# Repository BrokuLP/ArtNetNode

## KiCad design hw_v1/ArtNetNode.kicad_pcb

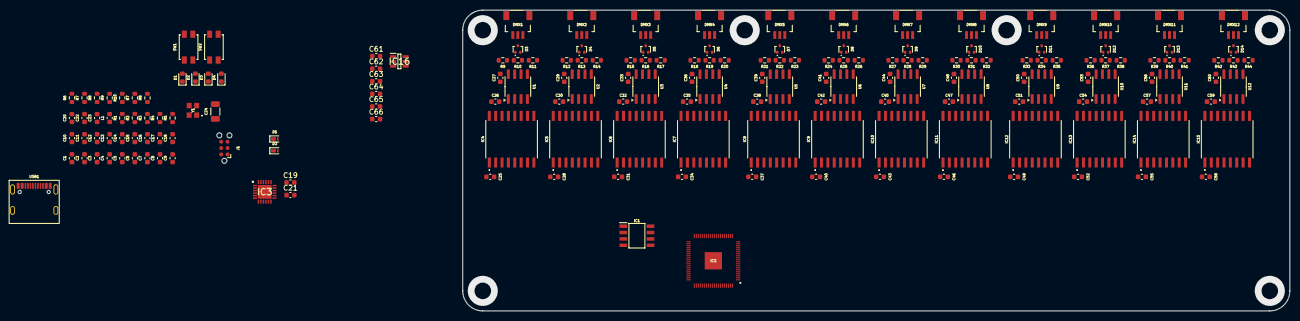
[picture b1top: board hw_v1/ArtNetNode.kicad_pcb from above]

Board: 4 copper layers, 165.0 x 60.0 mm, 178 parts (0 on the bottom side), 149 nets, no tracks yet.

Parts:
C1, C2, C6, C8, C9, C10, C11, C12, C13, C14, C15, C16, C17, C18, C19, C20, C21, C22, C23: 0u1/6V3; C_0603_1608Metric
C3, C4, C5, C7: 4u7/6V3; C_0603_1608Metric
C24: 1n/2kV; C_1206_3216Metric
C25, C26, C28, C29, C31, C32, C34, C35, C37, C38, C40, C41, C43, C44, C46, C47, C49, C50, C52, C53, C55, C56, C58, C59, C61, C62, C63, C64, C65, C66: 10u/6V3; C_0603_1608Metric
C27, C30, C33, C36, C39, C42, C45, C48, C51, C54, C57, C60: 1u/6V3; C_0603_1608Metric
D1, D2#2, D3#2, D4: LED; LED_0603_1608Metric
D1#2, D2: PTVS5V0Z1USK; Nexperia_DSN1608-2_1.6x0.8mm
D3, D4#2, D5, D6, D7, D8, D9, D10, D11, D12, D13, D14: RCLAMP0502B; SOT-416
DMX1, DMX2, DMX3, DMX4, DMX5, DMX6, DMX7, DMX8, DMX9, DMX10, DMX11, DMX12: SM03B-SRSS-TB_LF__SN_; SM03BSRSSTBLFSN
IC1: W25Q16JVSNIQ; SOIC127P600X175-8N
IC2: RP2350B; QFN40P1000X1000X90-81N-D
IC3: KTS1622EUAA-TR; QFN50P400X400X80-25N-D
IC4, IC5, IC6, IC7, IC8, IC9, IC10, IC11, IC12, IC13, IC14, IC15: 18024215401H
IC16: TPP361063-T6TR; SOT95P280X95-6N
J1: Conn_ARM_SWD_TagConnect_TC2030-NL; Tag-Connect_TC2030-IDC-NL_2x03_P1.27mm_Vertical
L1: 3u3; C_0603_1608Metric
R1, R7#2, R8, R9#2, R10: 10k; R_0603_1608Metric
R2, R6: 1k; R_0603_1608Metric
R3, R4: 27; R_0603_1608Metric
R5: 33; R_0603_1608Metric
R7, R8#2: 5k1; R_0603_1608Metric
R9, R10#2, R11, R12, R13, R14, R15, R16, R17, R18, R19, R20, R21, R22, R23, R24, R25, R26, R27, R28, R29, R30, R31, R32, R33, R34, R35, R36, R37, R38, R39, R40, R41, R42, R43, R44: R; R_0603_1608Metric
SW1, SW2: SW_SPST; SW_SPST_EVQP2
U1, U2, U3, U4, U5, U6, U7, U8, U9, U10, U11, U12: ST485E; SOIC-8_3.9x4.9mm_P1.27mm
USB1: USB4105-GF-A
Y1: SiT1602AC-13-33E-12.000000; SiT1602_2.5x2mm

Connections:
1V1: C4.1, C5.1, C6.1, C8.1, C9.1, IC2.10 (DVDD_1), IC2.32 (DVDD_2), IC2.51 (DVDD_3), IC2.65 (VREG_FB), L1.1
3V3: C1.1, C2.1, C3.1, C10.1, C11.1, C13.1, C14.1, C15.1, C16.1, C17.1, C18.1, C19.1, C20.1, C21.1, C22.1, C23.1, IC1.8 (VCC), IC2.5 (IOVDD_1), IC2.15 (IOVDD_2), IC2.24 (IOVDD_3), IC2.29 (IOVDD_4), IC2.41 (IOVDD_5), IC2.50 (IOVDD_6), IC2.59 (ADC_AVDD), IC2.60 (IOVDD_7), IC2.64 (VREG_VIN), IC2.68 (USB_OTP_VDD), IC2.69 (QSPI_IOVDD), IC2.76 (IOVDD_8), IC3.21 (VDD_P), IC3.23 (VDD_I2C), R1.1, R5.1, R6.1, Y1.1 (OE/~ST/NC), Y1.4 (VDD)
5V: J1.1 (VCC), USB1.A4 (VBUS), USB1.A9 (VBUS)
5V0: C25.1, C28.1, C31.1, C34.1, C37.1, C40.1, C43.1, C46.1, C49.1, C52.1, C55.1, C58.1, IC4.1 (VCC), IC5.1 (VCC), IC6.1 (VCC), IC7.1 (VCC), IC8.1 (VCC), IC9.1 (VCC), IC10.1 (VCC), IC11.1 (VCC), IC12.1 (VCC), IC13.1 (VCC), IC14.1 (VCC), IC15.1 (VCC)
/DMX0_RXD: IC2.13 (GPIO14), IC4.5 (OUTC)
/DMX0_TXD: IC2.11 (GPIO12), IC4.4 (INB)
/DMX0_TXE: IC2.12 (GPIO13), IC4.3 (INA)
/DMX1_RXD: IC2.17 (GPIO17), IC5.5 (OUTC)
/DMX1_TXD: IC2.16 (GPIO16), IC5.4 (INB)
/DMX1_TXE: IC2.14 (GPIO15), IC5.3 (INA)
/DMX2_RXD: IC2.20 (GPIO20), IC6.5 (OUTC)
/DMX2_TXD: IC2.18 (GPIO18), IC6.4 (INB)
/DMX2_TXE: IC2.19 (GPIO19), IC6.3 (INA)
/DMX3_RXD: IC2.23 (GPIO23), IC7.5 (OUTC)
/DMX3_TXD: IC2.21 (GPIO21), IC7.4 (INB)
/DMX3_TXE: IC2.22 (GPIO22), IC7.3 (INA)
/DMX4_RXD: IC2.27 (GPIO26), IC8.5 (OUTC)
/DMX4_TXD: IC2.25 (GPIO24), IC8.4 (INB)
/DMX4_TXE: IC2.26 (GPIO25), IC8.3 (INA)
/DMX5_RXD: IC2.37 (GPIO29), IC9.5 (OUTC)
/DMX5_TXD: IC2.28 (GPIO27), IC9.4 (INB)
/DMX5_TXE: IC2.36 (GPIO28), IC9.3 (INA)
/DMX6_RXD: IC2.40 (GPIO32), IC10.5 (OUTC)
/DMX6_TXD: IC2.38 (GPIO30), IC10.4 (INB)
/DMX6_TXE: IC2.39 (GPIO31), IC10.3 (INA)
/DMX7_RXD: IC2.44 (GPIO35), IC11.5 (OUTC)
/DMX7_TXD: IC2.42 (GPIO33), IC11.4 (INB)
/DMX7_TXE: IC2.43 (GPIO34), IC11.3 (INA)
/DMX8_RXD: IC2.47 (GPIO38), IC12.5 (OUTC)
/DMX8_TXD: IC2.45 (GPIO36), IC12.4 (INB)
/DMX8_TXE: IC2.46 (GPIO37), IC12.3 (INA)
/DMX9_RXD: IC2.52 (GPIO41_ADC1), IC13.5 (OUTC)
/DMX9_TXD: IC2.48 (GPIO39), IC13.4 (INB)
/DMX9_TXE: IC2.49 (GPIO40_ADC0), IC13.3 (INA)
/DMX10_RXD: IC2.55 (GPIO44_ADC4), IC14.5 (OUTC)
/DMX10_TXD: IC2.53 (GPIO42_ADC2), IC14.4 (INB)
/DMX10_TXE: IC2.54 (GPIO43_ADC3), IC14.3 (INA)
/DMX11_RXD: IC2.58 (GPIO47_ADC7), IC15.5 (OUTC)
/DMX11_TXD: IC2.56 (GPIO45_ADC5), IC15.4 (INB)
/DMX11_TXE: IC2.57 (GPIO46_ADC6), IC15.3 (INA)
/DMX_CH0/5V_DMX: C26.1, C27.1, IC4.10 (SEL), IC4.16 (VOUT), R9.1, U1.8 (VCC)
/DMX_CH0/DE_5V: IC4.14 (OUTA), U1.3 (DE)
/DMX_CH0/DI_5V: IC4.13 (OUTB), U1.4 (DI)
/DMX_CH0/DMX_N: D3.2 (K2), DMX1.1, R10#2.2, R11.1, U1.6 (A)
/DMX_CH0/DMX_P: D3.1 (K1), DMX1.3, R9.2, R10#2.1, U1.7 (B)
/DMX_CH0/GND_DMX: C26.2, C27.2, D3.3 (A), DMX1.2, DMX1.MP1, DMX1.MP2, IC4.9 (GND2_2), IC4.15 (GND2_1), R11.2, U1.2 (~RE), U1.5 (GND)
/DMX_CH0/RO_5V: IC4.12 (INC), U1.1 (RO)
/DMX_CH1/5V_DMX: C29.1, C30.1, IC5.10 (SEL), IC5.16 (VOUT), R12.1, U2.8 (VCC)
/DMX_CH1/DE_5V: IC5.14 (OUTA), U2.3 (DE)
/DMX_CH1/DI_5V: IC5.13 (OUTB), U2.4 (DI)
/DMX_CH1/DMX_N: D4#2.2 (K2), DMX2.1, R13.2, R14.1, U2.6 (A)
/DMX_CH1/DMX_P: D4#2.1 (K1), DMX2.3, R12.2, R13.1, U2.7 (B)
/DMX_CH1/GND_DMX: C29.2, C30.2, D4#2.3 (A), DMX2.2, DMX2.MP1, DMX2.MP2, IC5.9 (GND2_2), IC5.15 (GND2_1), R14.2, U2.2 (~RE), U2.5 (GND)
/DMX_CH1/RO_5V: IC5.12 (INC), U2.1 (RO)
/DMX_CH2/5V_DMX: C32.1, C33.1, IC6.10 (SEL), IC6.16 (VOUT), R15.1, U3.8 (VCC)
/DMX_CH2/DE_5V: IC6.14 (OUTA), U3.3 (DE)
/DMX_CH2/DI_5V: IC6.13 (OUTB), U3.4 (DI)
/DMX_CH2/DMX_N: D5.2 (K2), DMX3.1, R16.2, R17.1, U3.6 (A)
/DMX_CH2/DMX_P: D5.1 (K1), DMX3.3, R15.2, R16.1, U3.7 (B)
/DMX_CH2/GND_DMX: C32.2, C33.2, D5.3 (A), DMX3.2, DMX3.MP1, DMX3.MP2, IC6.9 (GND2_2), IC6.15 (GND2_1), R17.2, U3.2 (~RE), U3.5 (GND)
/DMX_CH2/RO_5V: IC6.12 (INC), U3.1 (RO)
/DMX_CH3/5V_DMX: C35.1, C36.1, IC7.10 (SEL), IC7.16 (VOUT), R18.1, U4.8 (VCC)
/DMX_CH3/DE_5V: IC7.14 (OUTA), U4.3 (DE)
/DMX_CH3/DI_5V: IC7.13 (OUTB), U4.4 (DI)
/DMX_CH3/DMX_N: D6.2 (K2), DMX4.1, R19.2, R20.1, U4.6 (A)
/DMX_CH3/DMX_P: D6.1 (K1), DMX4.3, R18.2, R19.1, U4.7 (B)
/DMX_CH3/GND_DMX: C35.2, C36.2, D6.3 (A), DMX4.2, DMX4.MP1, DMX4.MP2, IC7.9 (GND2_2), IC7.15 (GND2_1), R20.2, U4.2 (~RE), U4.5 (GND)
/DMX_CH3/RO_5V: IC7.12 (INC), U4.1 (RO)
/DMX_CH4/5V_DMX: C38.1, C39.1, IC8.10 (SEL), IC8.16 (VOUT), R21.1, U5.8 (VCC)
/DMX_CH4/DE_5V: IC8.14 (OUTA), U5.3 (DE)
/DMX_CH4/DI_5V: IC8.13 (OUTB), U5.4 (DI)
/DMX_CH4/DMX_N: D7.2 (K2), DMX5.1, R22.2, R23.1, U5.6 (A)
/DMX_CH4/DMX_P: D7.1 (K1), DMX5.3, R21.2, R22.1, U5.7 (B)
/DMX_CH4/GND_DMX: C38.2, C39.2, D7.3 (A), DMX5.2, DMX5.MP1, DMX5.MP2, IC8.9 (GND2_2), IC8.15 (GND2_1), R23.2, U5.2 (~RE), U5.5 (GND)
/DMX_CH4/RO_5V: IC8.12 (INC), U5.1 (RO)
/DMX_CH5/5V_DMX: C41.1, C42.1, IC9.10 (SEL), IC9.16 (VOUT), R24.1, U6.8 (VCC)
/DMX_CH5/DE_5V: IC9.14 (OUTA), U6.3 (DE)
/DMX_CH5/DI_5V: IC9.13 (OUTB), U6.4 (DI)
/DMX_CH5/DMX_N: D8.2 (K2), DMX6.1, R25.2, R26.1, U6.6 (A)
/DMX_CH5/DMX_P: D8.1 (K1), DMX6.3, R24.2, R25.1, U6.7 (B)
/DMX_CH5/GND_DMX: C41.2, C42.2, D8.3 (A), DMX6.2, DMX6.MP1, DMX6.MP2, IC9.9 (GND2_2), IC9.15 (GND2_1), R26.2, U6.2 (~RE), U6.5 (GND)
/DMX_CH5/RO_5V: IC9.12 (INC), U6.1 (RO)
/DMX_CH6/5V_DMX: C44.1, C45.1, IC10.10 (SEL), IC10.16 (VOUT), R27.1, U7.8 (VCC)
/DMX_CH6/DE_5V: IC10.14 (OUTA), U7.3 (DE)
/DMX_CH6/DI_5V: IC10.13 (OUTB), U7.4 (DI)
/DMX_CH6/DMX_N: D9.2 (K2), DMX7.1, R28.2, R29.1, U7.6 (A)
/DMX_CH6/DMX_P: D9.1 (K1), DMX7.3, R27.2, R28.1, U7.7 (B)
/DMX_CH6/GND_DMX: C44.2, C45.2, D9.3 (A), DMX7.2, DMX7.MP1, DMX7.MP2, IC10.9 (GND2_2), IC10.15 (GND2_1), R29.2, U7.2 (~RE), U7.5 (GND)
/DMX_CH6/RO_5V: IC10.12 (INC), U7.1 (RO)
/DMX_CH7/5V_DMX: C47.1, C48.1, IC11.10 (SEL), IC11.16 (VOUT), R30.1, U8.8 (VCC)
/DMX_CH7/DE_5V: IC11.14 (OUTA), U8.3 (DE)
/DMX_CH7/DI_5V: IC11.13 (OUTB), U8.4 (DI)
/DMX_CH7/DMX_N: D10.2 (K2), DMX8.1, R31.2, R32.1, U8.6 (A)
/DMX_CH7/DMX_P: D10.1 (K1), DMX8.3, R30.2, R31.1, U8.7 (B)
/DMX_CH7/GND_DMX: C47.2, C48.2, D10.3 (A), DMX8.2, DMX8.MP1, DMX8.MP2, IC11.9 (GND2_2), IC11.15 (GND2_1), R32.2, U8.2 (~RE), U8.5 (GND)
/DMX_CH7/RO_5V: IC11.12 (INC), U8.1 (RO)
/DMX_CH8/5V_DMX: C50.1, C51.1, IC12.10 (SEL), IC12.16 (VOUT), R33.1, U9.8 (VCC)
/DMX_CH8/DE_5V: IC12.14 (OUTA), U9.3 (DE)
/DMX_CH8/DI_5V: IC12.13 (OUTB), U9.4 (DI)
/DMX_CH8/DMX_N: D11.2 (K2), DMX9.1, R34.2, R35.1, U9.6 (A)
/DMX_CH8/DMX_P: D11.1 (K1), DMX9.3, R33.2, R34.1, U9.7 (B)
/DMX_CH8/GND_DMX: C50.2, C51.2, D11.3 (A), DMX9.2, DMX9.MP1, DMX9.MP2, IC12.9 (GND2_2), IC12.15 (GND2_1), R35.2, U9.2 (~RE), U9.5 (GND)
/DMX_CH8/RO_5V: IC12.12 (INC), U9.1 (RO)
/DMX_CH9/5V_DMX: C53.1, C54.1, IC13.10 (SEL), IC13.16 (VOUT), R36.1, U10.8 (VCC)
/DMX_CH9/DE_5V: IC13.14 (OUTA), U10.3 (DE)
/DMX_CH9/DI_5V: IC13.13 (OUTB), U10.4 (DI)
/DMX_CH9/DMX_N: D12.2 (K2), DMX10.1, R37.2, R38.1, U10.6 (A)
/DMX_CH9/DMX_P: D12.1 (K1), DMX10.3, R36.2, R37.1, U10.7 (B)
/DMX_CH9/GND_DMX: C53.2, C54.2, D12.3 (A), DMX10.2, DMX10.MP1, DMX10.MP2, IC13.9 (GND2_2), IC13.15 (GND2_1), R38.2, U10.2 (~RE), U10.5 (GND)
/DMX_CH9/RO_5V: IC13.12 (INC), U10.1 (RO)
/DMX_CH10/5V_DMX: C56.1, C57.1, IC14.10 (SEL), IC14.16 (VOUT), R39.1, U11.8 (VCC)
/DMX_CH10/DE_5V: IC14.14 (OUTA), U11.3 (DE)
/DMX_CH10/DI_5V: IC14.13 (OUTB), U11.4 (DI)
/DMX_CH10/DMX_N: D13.2 (K2), DMX11.1, R40.2, R41.1, U11.6 (A)
/DMX_CH10/DMX_P: D13.1 (K1), DMX11.3, R39.2, R40.1, U11.7 (B)
/DMX_CH10/GND_DMX: C56.2, C57.2, D13.3 (A), DMX11.2, DMX11.MP1, DMX11.MP2, IC14.9 (GND2_2), IC14.15 (GND2_1), R41.2, U11.2 (~RE), U11.5 (GND)
/DMX_CH10/RO_5V: IC14.12 (INC), U11.1 (RO)
/DMX_CH11/5V_DMX: C59.1, C60.1, IC15.10 (SEL), IC15.16 (VOUT), R42.1, U12.8 (VCC)
/DMX_CH11/DE_5V: IC15.14 (OUTA), U12.3 (DE)
/DMX_CH11/DI_5V: IC15.13 (OUTB), U12.4 (DI)
/DMX_CH11/DMX_N: D14.2 (K2), DMX12.1, R43.2, R44.1, U12.6 (A)
/DMX_CH11/DMX_P: D14.1 (K1), DMX12.3, R42.2, R43.1, U12.7 (B)
/DMX_CH11/GND_DMX: C59.2, C60.2, D14.3 (A), DMX12.2, DMX12.MP1, DMX12.MP2, IC15.9 (GND2_2), IC15.15 (GND2_1), R44.2, U12.2 (~RE), U12.5 (GND)
/DMX_CH11/RO_5V: IC15.12 (INC), U12.1 (RO)
/MCU/DEV_RST: IC2.8 (GPIO10), IC3.24 (~RESET)
/MCU/EXP_INT: IC2.7 (GPIO9), IC3.22 (~INT)
/MCU/I2C_SCL: IC2.4 (GPIO7), IC3.19 (SCL)
/MCU/I2C_SDA: IC2.6 (GPIO8), IC3.20 (SDA)
/MCU/QSPI_SCLK: IC1.6 (CLK), IC2.71 (QSPI_SCLK)
/MCU/QSPI_SD0: IC1.5 (DI_(IO0)), IC2.72 (QSPI_SD0)
/MCU/QSPI_SD1: IC1.2 (DO_(IO1)), IC2.74 (QSPI_SD1)
/MCU/QSPI_SD2: IC1.3 (~WP_(IO2)), IC2.73 (QSPI_SD2)
/MCU/QSPI_SD3: IC1.7 (~HOLD_OR_/RESET_(IO3)), IC2.70 (QSPI_SD3)
/MCU/QSPI_SS: IC1.1 (~CS), IC2.75 (QSPI_SS), R1.2, R2.1
/MCU/RUN: C12.1, IC2.35 (RUN), J1.3 (~RESET), R6.2, SW2.2 (B)
/MCU/SWCLK: IC2.33 (SWCLK), J1.4 (SWCLK)
/MCU/SWD: IC2.34 (SWDIO), J1.2 (SWDIO)
/MCU/USB_DN: D2.1 (K), R4.1, USB1.A7 (DN1), USB1.B7 (DN2)
/MCU/USB_DP: D1#2.1 (K), R3.1, USB1.A6 (DP1), USB1.B6 (DP2)
/MCU/~USB_BOOT: R2.2, SW1.2 (B)
GND: C1.2, C2.2, C3.2, C4.2, C6.2, C7.2, C8.2, C9.2, C10.2, C11.2, C12.2, C13.2, C14.2, C15.2, C16.2, C17.2, C18.2, C19.2, C20.2, C21.2, C22.2, C23.2, C24.1, C25.2, C28.2, C31.2, C34.2, C37.2, C40.2, C43.2, C46.2, C49.2, C52.2, C55.2, C58.2, D1#2.2 (A), D2.2 (A), IC1.4 (GND), IC2.62 (VREG_PGND), IC2.81 (GND), IC3.9 (GND), IC4.2 (GND1_1), IC4.8 (GND1_2), IC5.2 (GND1_1), IC5.8 (GND1_2), IC6.2 (GND1_1), IC6.8 (GND1_2), IC7.2 (GND1_1), IC7.8 (GND1_2), IC8.2 (GND1_1), IC8.8 (GND1_2), IC9.2 (GND1_1), IC9.8 (GND1_2), IC10.2 (GND1_1), IC10.8 (GND1_2), IC11.2 (GND1_1), IC11.8 (GND1_2), IC12.2 (GND1_1), IC12.8 (GND1_2), IC13.2 (GND1_1), IC13.8 (GND1_2), IC14.2 (GND1_1), IC14.8 (GND1_2), IC15.2 (GND1_1), IC15.8 (GND1_2), IC16.2 (GND), J1.5 (GND), R7.1, R8#2.1, SW1.1 (A), SW2.1 (A), USB1.A1 (GND), USB1.A12 (GND), Y1.2 (GND)
unnamed: IC2.66 (USB_DM), R3.2
unnamed: IC2.67 (USB_DP), R4.2
unnamed: C7.1, IC2.61 (VREG_AVDD), R5.2
unnamed: C5.2, IC2.63 (VREG_LX), L1.2
unnamed: IC2.30 (XIN), Y1.3 (OUT)
unnamed: R7.2, USB1.A5 (CC1)
unnamed: R8#2.2, USB1.B5 (CC2)
unnamed: C24.2, USB1.SH (SHIELD)

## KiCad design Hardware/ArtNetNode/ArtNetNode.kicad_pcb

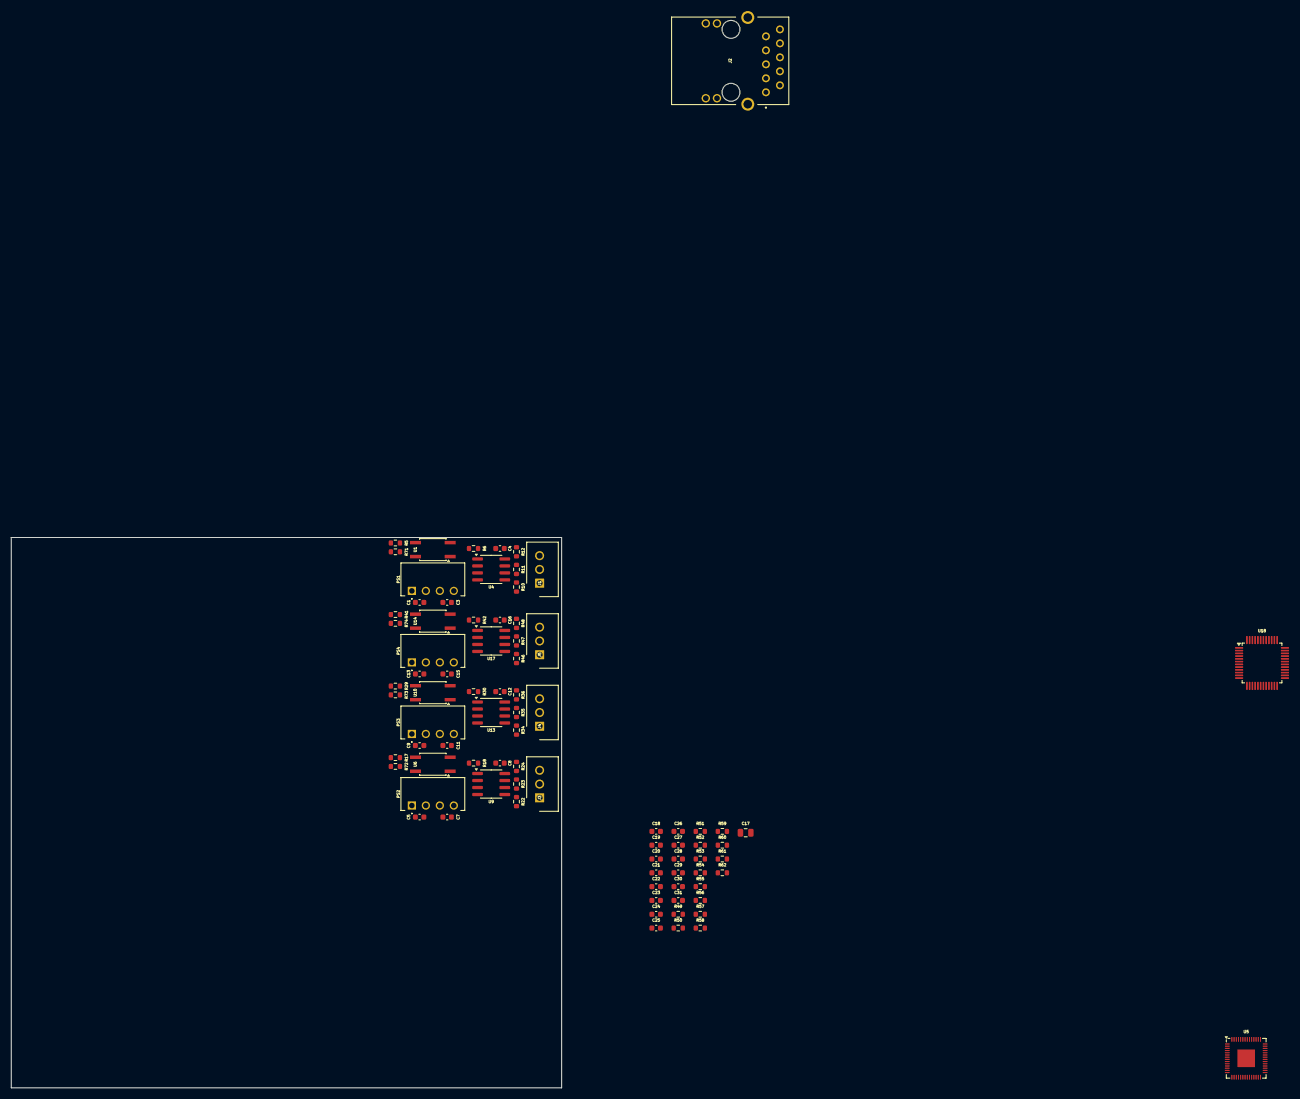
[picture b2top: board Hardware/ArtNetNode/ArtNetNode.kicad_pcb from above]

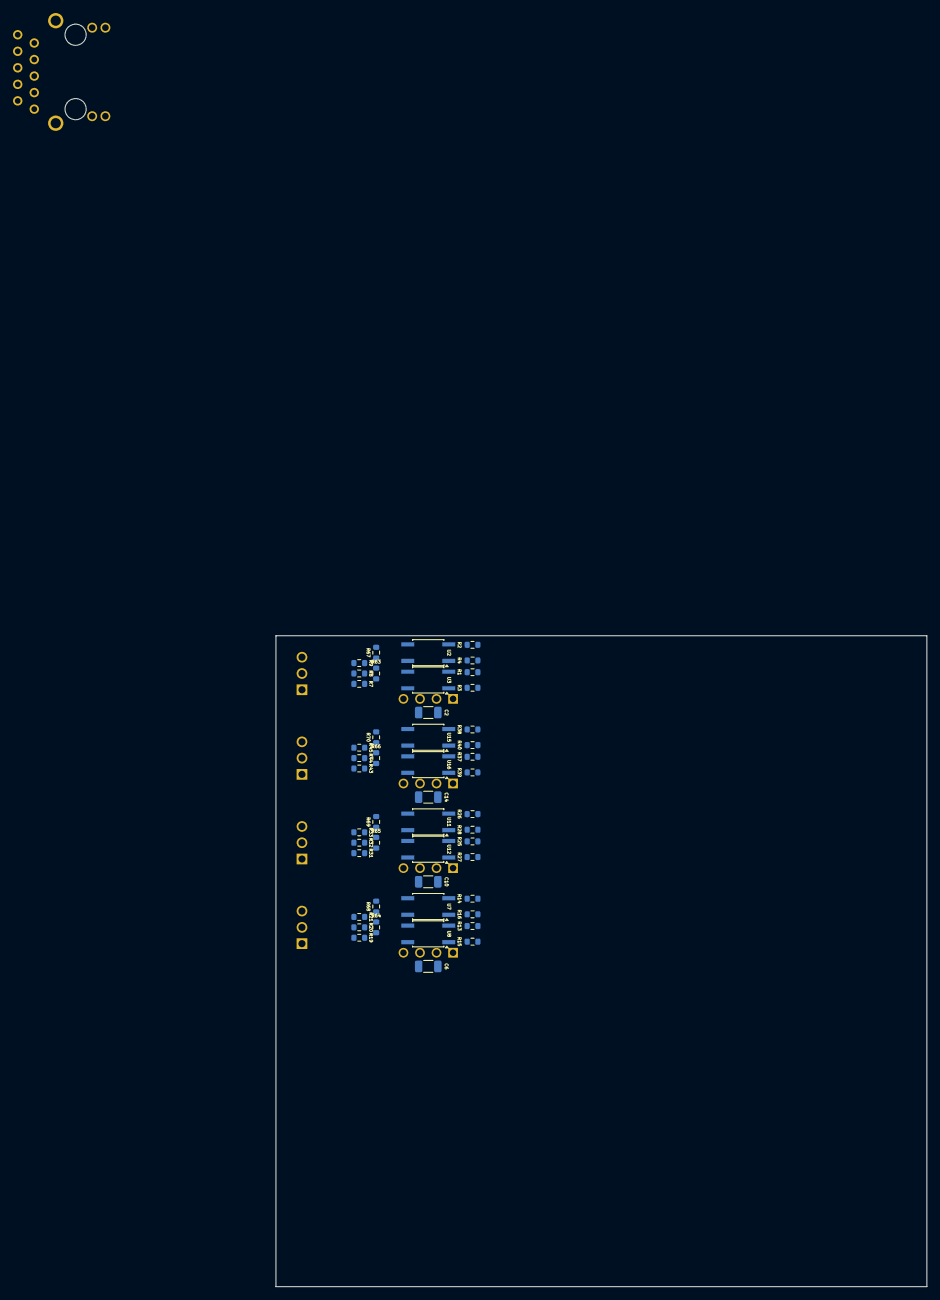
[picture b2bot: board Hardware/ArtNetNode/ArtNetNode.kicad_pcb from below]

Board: 2 copper layers, 100.0 x 100.0 mm, 132 parts (48 on the bottom side), 77 nets, no tracks yet.

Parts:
C1, C3, C4, C5, C7, C8, C9, C11, C12, C13, C15, C16: 2u2/6V3; C_0603_1608Metric
C2, C6, C10, C14: 470p/2kV; C_1206_3216Metric
C17: 10u/6V3; C_0805_2012Metric
C18, C19, C20, C21, C22, C23, C24, C25, C26: 0u1/6V3; C_0603_1608Metric
C27: 10u/6V3; C_0603_1608Metric
C28: 10n/63V; C_0603_1608Metric
C29: 22n/62V; C_0603_1608Metric
C30, C31: 6n8/63V; C_0603_1608Metric
J1, J3, J4, J5: B3B-XH-A
J2: ARJM11D7-104-AB-EW2; ARJM11D7104ABEW2
PS1, PS2, PS3, PS4: 1S4E_0505S1.5U; 1S4E_0505S15U
R1, R2, R5, R7, R8, R9, R13, R14, R17, R19, R20, R21, R25, R26, R29, R31, R32, R33, R37, R38, R41, R43, R44, R45, R71, R72, R73, R74: 10k; R_0603_1608Metric
R3, R4, R6, R15, R16, R18, R27, R28, R30, R39, R40, R42: 100; R_0603_1608Metric
R10, R12, R22, R24, R34, R36, R46, R48: 100k; R_0603_1608Metric
R11, R23, R35, R47: 120; R_0603_1608Metric
R49: 12k4; R_0603_1608Metric
R50, R51, R52, R53: 330; R_0603_1608Metric
R54, R55, R56, R57, R63, R64, R65, R66, R67, R68, R69, R70: 0; R_0603_1608Metric
R58, R59, R60, R61: 49R9; R_0603_1608Metric
R62: 10R; R_0603_1608Metric
U1, U2, U3, U6, U7, U8, U10, U11, U12, U14, U15, U16: LTV-356T; SO-4_4.4x3.6mm_P2.54mm
U4, U9, U13, U17: MAX485E; SOIC-8_3.9x4.9mm_P1.27mm
U5: RP2040; QFN-56-1EP_7x7mm_P0.4mm_EP3.2x3.2mm
U18: W5500; LQFP-48_7x7mm_P0.5mm

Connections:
+3.3V: R1.1, R2.1, R3.2, R4.2, R13.1, R14.1, R15.2, R16.2, R25.1, R26.1, R27.2, R28.2, R37.1, R38.1, R39.2, R40.2, R71.1, R72.1, R73.1, R74.1, U1.4, U6.4, U10.4, U14.4
+3V3: C17.1, C18.1, C19.1, C21.1, C23.1, C24.1, C25.1, C26.1, C27.1, R58.2, R60.2, R62.1, U18.4 (AVDD), U18.8 (AVDD), U18.11 (AVDD), U18.15 (AVDD), U18.17 (AVDD), U18.21 (AVDD), U18.28 (VDD)
+5V: C1.1, C5.1, C9.1, C13.1, PS1.2 (VI+), PS2.2 (VI+), PS3.2 (VI+), PS4.2 (VI+)
/DMX_DRIVER0/DIR: R2.2, U2.2
/DMX_DRIVER0/ISO_5V: C3.1, C4.1, PS1.4 (VO+), R7.1, R8.1, R9.1, R10.1, U4.8 (VCC)
/DMX_DRIVER0/ISO_GND: C2.2, C3.2, C4.2, J1.2, PS1.3 (VO-), R12.2, R67.2, U1.2, U2.3, U3.3, U4.5 (GND)
/DMX_DRIVER0/RX: R5.1, R71.2, U1.3
/DMX_DRIVER0/TX: R1.2, U3.2
/DMX_DRIVER1/DIR: R14.2, U7.2
/DMX_DRIVER1/ISO_5V: C7.1, C8.1, PS2.4 (VO+), R19.1, R20.1, R21.1, R22.1, U9.8 (VCC)
/DMX_DRIVER1/ISO_GND: C6.2, C7.2, C8.2, J3.2, PS2.3 (VO-), R24.2, R68.2, U6.2, U7.3, U8.3, U9.5 (GND)
/DMX_DRIVER1/RX: R17.1, R72.2, U6.3
/DMX_DRIVER1/TX: R13.2, U8.2
/DMX_DRIVER2/DIR: R26.2, U11.2
/DMX_DRIVER2/ISO_5V: C11.1, C12.1, PS3.4 (VO+), R31.1, R32.1, R33.1, R34.1, U13.8 (VCC)
/DMX_DRIVER2/ISO_GND: C10.2, C11.2, C12.2, J4.2, PS3.3 (VO-), R36.2, R69.2, U10.2, U11.3, U12.3, U13.5 (GND)
/DMX_DRIVER2/RX: R29.1, R73.2, U10.3
/DMX_DRIVER2/TX: R25.2, U12.2
/DMX_DRIVER3/DIR: R38.2, U15.2
/DMX_DRIVER3/ISO_5V: C15.1, C16.1, PS4.4 (VO+), R43.1, R44.1, R45.1, R46.1, U17.8 (VCC)
/DMX_DRIVER3/ISO_GND: C14.2, C15.2, C16.2, J5.2, PS4.3 (VO-), R48.2, R70.2, U14.2, U15.3, U16.3, U17.5 (GND)
/DMX_DRIVER3/RX: R41.1, R74.2, U14.3
/DMX_DRIVER3/TX: R37.2, U16.2
/ETHERNET/PHY/RCT: C28.1, R59.1, R61.1
/ETHERNET/PHY/RX_N: R56.1, U18.5 (RXN)
/ETHERNET/PHY/RX_P: R57.1, U18.6 (RXP)
/ETHERNET/PHY/TCT: C29.1, R54.2, R55.2, R58.1, R60.1, R62.2
/ETHERNET/PHY/TX_N: R54.1, U18.1 (TXN)
/ETHERNET/PHY/TX_P: R55.1, U18.2 (TXP)
GND: C1.2, C2.1, C5.2, C6.1, C9.2, C10.1, C13.2, C14.1, C17.2, C18.2, C19.2, C20.2, C21.2, C22.2, C23.2, C24.2, C25.2, C26.2, C27.2, C28.2, C29.2, PS1.1 (VI-), PS2.1 (VI-), PS3.1 (VI-), PS4.1 (VI-), R5.2, R17.2, R29.2, R41.2, R49.1, U18.3 (AGND), U18.9 (AGND), U18.14 (AGND), U18.16 (AGND), U18.19 (AGND), U18.29 (GND), U18.48 (AGND)
unnamed: C30.2, R56.2
unnamed: C31.1, R57.2, R59.2, R61.2
unnamed: R3.1, U3.1
unnamed: R4.1, U2.1
unnamed: R6.1, U1.1
unnamed: R15.1, U8.1
unnamed: R16.1, U7.1
unnamed: R18.1, U6.1
unnamed: R27.1, U12.1
unnamed: R28.1, U11.1
unnamed: R30.1, U10.1
unnamed: R39.1, U16.1
unnamed: R40.1, U15.1
unnamed: R42.1, U14.1
unnamed: J1.1, R10.2, R11.1, U4.6 (A)
unnamed: J1.3, R11.2, R12.1, U4.7 (B)
unnamed: R8.2, R63.2, U2.4, U4.3 (DE)
unnamed: R7.2, U3.4, U4.4 (DI)
unnamed: R6.2, R9.2, U4.1 (RO)
unnamed: R63.1, R67.1, U4.2 (~RE)
unnamed: U5.23 (DVDD), U5.50 (DVDD)
unnamed: U5.1 (IOVDD), U5.10 (IOVDD), U5.22 (IOVDD), U5.33 (IOVDD), U5.42 (IOVDD), U5.49 (IOVDD)
unnamed: J3.1, R22.2, R23.1, U9.6 (A)
unnamed: J3.3, R23.2, R24.1, U9.7 (B)
unnamed: R20.2, R64.2, U7.4, U9.3 (DE)
unnamed: R19.2, U8.4, U9.4 (DI)
unnamed: R18.2, R21.2, U9.1 (RO)
unnamed: R64.1, R68.1, U9.2 (~RE)
unnamed: J4.1, R34.2, R35.1, U13.6 (A)
unnamed: J4.3, R35.2, R36.1, U13.7 (B)
unnamed: R32.2, R65.2, U11.4, U13.3 (DE)
unnamed: R31.2, U12.4, U13.4 (DI)
unnamed: R30.2, R33.2, U13.1 (RO)
unnamed: R65.1, R69.1, U13.2 (~RE)
unnamed: J5.1, R46.2, R47.1, U17.6 (A)
unnamed: J5.3, R47.2, R48.1, U17.7 (B)
unnamed: R44.2, R66.2, U15.4, U17.3 (DE)
unnamed: R43.2, U16.4, U17.4 (DI)
unnamed: R42.2, R45.2, U17.1 (RO)
unnamed: R66.1, R70.1, U17.2 (~RE)
unnamed: C20.1, U18.22 (1V2O)
unnamed: R53.1, U18.27 (ACTLED)
unnamed: R52.1, U18.26 (DUPLED)
unnamed: R49.2, U18.10 (EXRES1)
unnamed: R51.1, U18.25 (LINKLED)
unnamed: R50.1, U18.24 (SPDLED)
unnamed: C22.1, U18.20 (TOCAP)

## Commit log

2024-05-18 init
2024-05-18 added librarys
2024-05-24 added usb lib
2024-11-30 moved firmware to own folder
2024-11-30 started project and added dmx driver
2024-12-01 added ethernet
2024-12-05 finished dmx interfaces
2025-12-23 removed unused files
2025-12-23 started schematics
2025-12-25 started hardware
2025-12-25 started firmware
2025-12-25 started KTS1622 driver
2025-12-26 started stm7735 driver
2025-12-26 added dmx512 lib
2025-12-26 added pico sdk and started cmake file
2025-12-26 added artnet library
